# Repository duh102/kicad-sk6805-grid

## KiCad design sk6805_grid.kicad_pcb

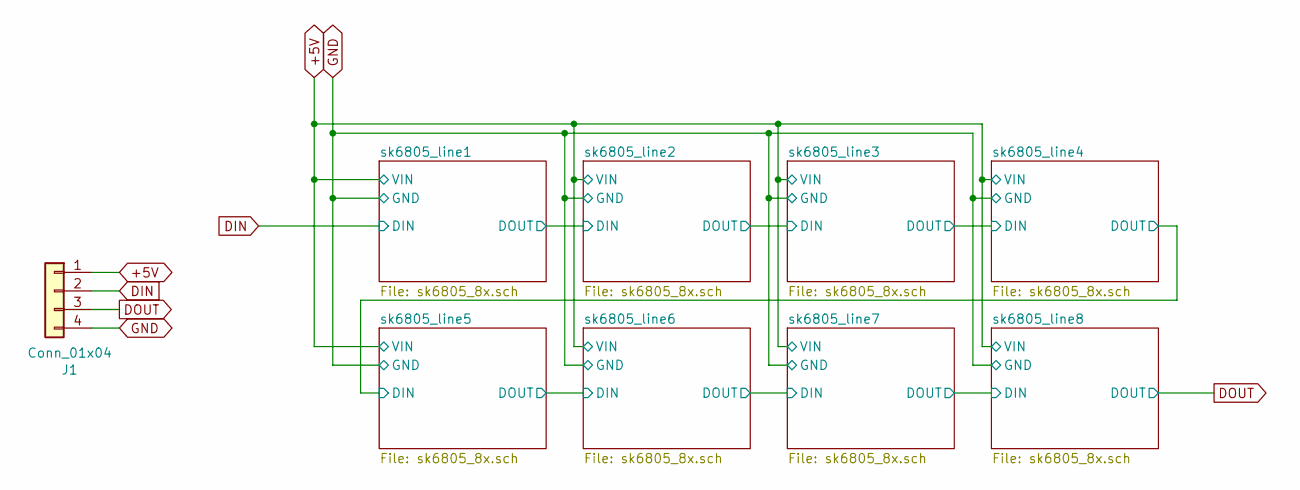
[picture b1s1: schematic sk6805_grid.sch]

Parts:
J1: Conn_01x04; PinHeader_1x04_P2.54mm_Vertical

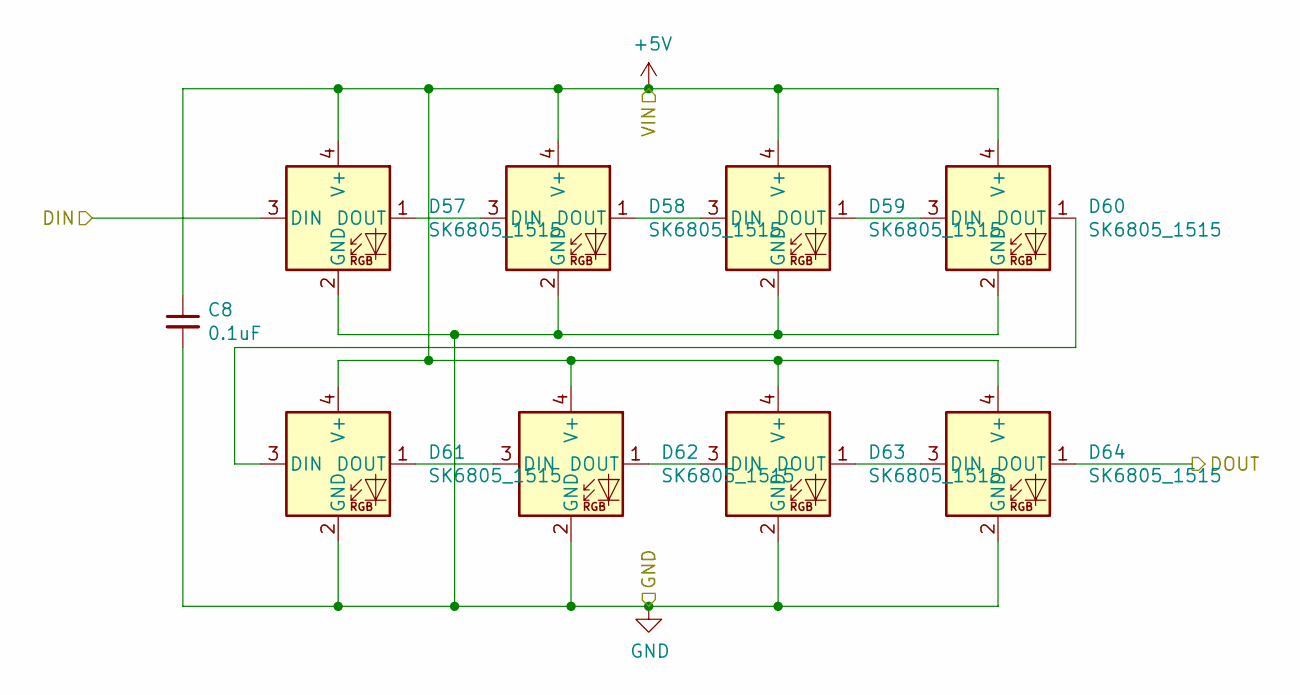
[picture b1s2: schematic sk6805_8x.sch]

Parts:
C1: 0.1uF; C_0805_2012Metric
D1, D2, D3, D4, D5, D6, D7, D8: SK6805_1515; LED_SK6805_PLCC4_1.5x1.5mm_P0.65mm

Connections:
+5V: C1.1, D1.4 (V+), D2.4 (V+), D3.4 (V+), D4.4 (V+), D5.4 (V+), D6.4 (V+), D7.4 (V+), D8.4 (V+); also elsewhere on the board
/sk6805_line2/DIN: D8.1 (DOUT); also elsewhere on the board
DIN: D1.3 (DIN); also elsewhere on the board
GND: C1.2, D1.2 (GND), D2.2 (GND), D3.2 (GND), D4.2 (GND), D5.2 (GND), D6.2 (GND), D7.2 (GND), D8.2 (GND); also elsewhere on the board
unnamed: D1.1 (DOUT), D2.3 (DIN)
unnamed: D2.1 (DOUT), D3.3 (DIN)
unnamed: D3.1 (DOUT), D4.3 (DIN)
unnamed: D4.1 (DOUT), D5.3 (DIN)
unnamed: D5.1 (DOUT), D6.3 (DIN)
unnamed: D6.1 (DOUT), D7.3 (DIN)
unnamed: D7.1 (DOUT), D8.3 (DIN)

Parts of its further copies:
C2, C3, C4, C5, C6, C7, C8: 0.1uF; C_0805_2012Metric
D9, D10, D11, D12, D13, D14, D15, D16, D17, D18, D19, D20, D21, D22, D23, D24, D25, D26, D27, D28, D29, D30, D31, D32, D33, D34, D35, D36, D37, D38, D39, D40, D41, D42, D43, D44, D45, D46, D47, D48, D49, D50, D51, D52, D53, D54, D55, D56, D57, D58, D59, D60, D61, D62, D63, D64: SK6805_1515; LED_SK6805_PLCC4_1.5x1.5mm_P0.65mm

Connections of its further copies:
+5V: C2.1, C3.1, C4.1, C5.1, C6.1, C7.1, C8.1, D9.4 (V+), D10.4 (V+), D11.4 (V+), D12.4 (V+), D13.4 (V+), D14.4 (V+), D15.4 (V+), D16.4 (V+), D17.4 (V+), D18.4 (V+), D19.4 (V+), D20.4 (V+), D21.4 (V+), D22.4 (V+), D23.4 (V+), D24.4 (V+), D25.4 (V+), D26.4 (V+), D27.4 (V+), D28.4 (V+), D29.4 (V+), D30.4 (V+), D31.4 (V+), D32.4 (V+), D33.4 (V+), D34.4 (V+), D35.4 (V+), D36.4 (V+), D37.4 (V+), D38.4 (V+), D39.4 (V+), D40.4 (V+), D41.4 (V+), D42.4 (V+), D43.4 (V+), D44.4 (V+), D45.4 (V+), D46.4 (V+), D47.4 (V+), D48.4 (V+), D49.4 (V+), D50.4 (V+), D51.4 (V+), D52.4 (V+), D53.4 (V+), D54.4 (V+), D55.4 (V+), D56.4 (V+), D57.4 (V+), D58.4 (V+), D59.4 (V+), D60.4 (V+), D61.4 (V+), D62.4 (V+), D63.4 (V+), D64.4 (V+); also elsewhere on the board
/sk6805_line2/DIN: D9.3 (DIN); also elsewhere on the board
/sk6805_line3/DIN: D16.1 (DOUT), D17.3 (DIN)
/sk6805_line4/DIN: D24.1 (DOUT), D25.3 (DIN)
/sk6805_line5/DIN: D32.1 (DOUT), D33.3 (DIN)
/sk6805_line6/DIN: D40.1 (DOUT), D41.3 (DIN)
/sk6805_line7/DIN: D48.1 (DOUT), D49.3 (DIN)
/sk6805_line8/DIN: D56.1 (DOUT), D57.3 (DIN)
DOUT: D64.1 (DOUT); also elsewhere on the board
GND: C2.2, C3.2, C4.2, C5.2, C6.2, C7.2, C8.2, D9.2 (GND), D10.2 (GND), D11.2 (GND), D12.2 (GND), D13.2 (GND), D14.2 (GND), D15.2 (GND), D16.2 (GND), D17.2 (GND), D18.2 (GND), D19.2 (GND), D20.2 (GND), D21.2 (GND), D22.2 (GND), D23.2 (GND), D24.2 (GND), D25.2 (GND), D26.2 (GND), D27.2 (GND), D28.2 (GND), D29.2 (GND), D30.2 (GND), D31.2 (GND), D32.2 (GND), D33.2 (GND), D34.2 (GND), D35.2 (GND), D36.2 (GND), D37.2 (GND), D38.2 (GND), D39.2 (GND), D40.2 (GND), D41.2 (GND), D42.2 (GND), D43.2 (GND), D44.2 (GND), D45.2 (GND), D46.2 (GND), D47.2 (GND), D48.2 (GND), D49.2 (GND), D50.2 (GND), D51.2 (GND), D52.2 (GND), D53.2 (GND), D54.2 (GND), D55.2 (GND), D56.2 (GND), D57.2 (GND), D58.2 (GND), D59.2 (GND), D60.2 (GND), D61.2 (GND), D62.2 (GND), D63.2 (GND), D64.2 (GND); also elsewhere on the board
unnamed: D10.1 (DOUT), D11.3 (DIN)
unnamed: D9.1 (DOUT), D10.3 (DIN)
unnamed: D11.1 (DOUT), D12.3 (DIN)
unnamed: D12.1 (DOUT), D13.3 (DIN)
unnamed: D13.1 (DOUT), D14.3 (DIN)
unnamed: D14.1 (DOUT), D15.3 (DIN)
unnamed: D15.1 (DOUT), D16.3 (DIN)
unnamed: D17.1 (DOUT), D18.3 (DIN)
unnamed: D18.1 (DOUT), D19.3 (DIN)
unnamed: D19.1 (DOUT), D20.3 (DIN)
unnamed: D20.1 (DOUT), D21.3 (DIN)
unnamed: D21.1 (DOUT), D22.3 (DIN)
unnamed: D22.1 (DOUT), D23.3 (DIN)
unnamed: D23.1 (DOUT), D24.3 (DIN)
unnamed: D25.1 (DOUT), D26.3 (DIN)
unnamed: D26.1 (DOUT), D27.3 (DIN)
unnamed: D27.1 (DOUT), D28.3 (DIN)
unnamed: D28.1 (DOUT), D29.3 (DIN)
unnamed: D29.1 (DOUT), D30.3 (DIN)
unnamed: D30.1 (DOUT), D31.3 (DIN)
unnamed: D31.1 (DOUT), D32.3 (DIN)
unnamed: D33.1 (DOUT), D34.3 (DIN)
unnamed: D34.1 (DOUT), D35.3 (DIN)
unnamed: D35.1 (DOUT), D36.3 (DIN)
unnamed: D36.1 (DOUT), D37.3 (DIN)
unnamed: D37.1 (DOUT), D38.3 (DIN)
unnamed: D38.1 (DOUT), D39.3 (DIN)
unnamed: D39.1 (DOUT), D40.3 (DIN)
unnamed: D41.1 (DOUT), D42.3 (DIN)
unnamed: D42.1 (DOUT), D43.3 (DIN)
unnamed: D43.1 (DOUT), D44.3 (DIN)
unnamed: D44.1 (DOUT), D45.3 (DIN)
unnamed: D45.1 (DOUT), D46.3 (DIN)
unnamed: D46.1 (DOUT), D47.3 (DIN)
unnamed: D47.1 (DOUT), D48.3 (DIN)
unnamed: D49.1 (DOUT), D50.3 (DIN)
unnamed: D50.1 (DOUT), D51.3 (DIN)
unnamed: D51.1 (DOUT), D52.3 (DIN)
unnamed: D52.1 (DOUT), D53.3 (DIN)
unnamed: D53.1 (DOUT), D54.3 (DIN)
unnamed: D54.1 (DOUT), D55.3 (DIN)
unnamed: D55.1 (DOUT), D56.3 (DIN)
unnamed: D57.1 (DOUT), D58.3 (DIN)
unnamed: D58.1 (DOUT), D59.3 (DIN)
unnamed: D59.1 (DOUT), D60.3 (DIN)
unnamed: D60.1 (DOUT), D61.3 (DIN)
unnamed: D61.1 (DOUT), D62.3 (DIN)
unnamed: D62.1 (DOUT), D63.3 (DIN)
unnamed: D63.1 (DOUT), D64.3 (DIN)

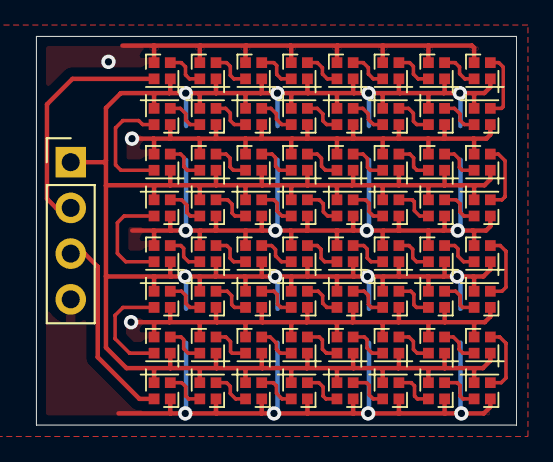
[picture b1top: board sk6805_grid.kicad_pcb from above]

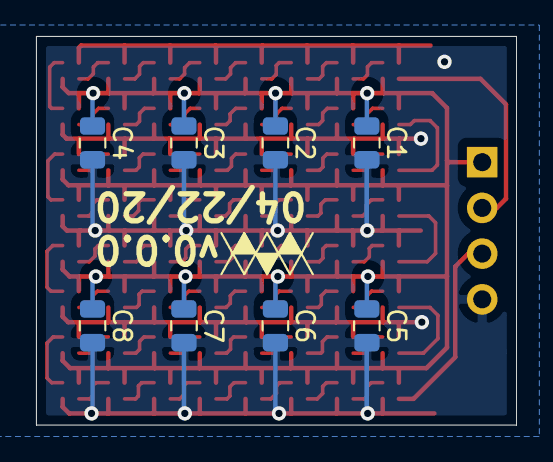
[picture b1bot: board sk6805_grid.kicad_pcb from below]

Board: 2 copper layers, 26.7 x 21.6 mm, 73 parts (8 on the bottom side), 67 nets.

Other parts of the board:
Je: Conn_01x04; PinHeader_1x04_P2.54mm_Vertical

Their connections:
+5V: Je.1; also elsewhere on the board
DIN: Je.2; also elsewhere on the board
DOUT: Je.3; also elsewhere on the board
GND: Je.4; also elsewhere on the board

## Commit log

2020-04-22 Finish most of the design
2020-04-22 Add logo and version stamp
2020-12-09 Add gbr output
